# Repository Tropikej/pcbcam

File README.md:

# pcbcam

KiCad project + versioned YAML recipe → checked, machine-ready G-code for PCB
isolation milling on a **Makera Z1**, using [pcb2gcode](https://github.com/pcb2gcode/pcb2gcode)
as the CAM engine.

> **Status: v0.1, verified on a Makera Z1 (2026-11-09).** A full double-sided
> board — front + back isolation, drilling, registration bores and the tabbed
> outline — cuts and registers through the flip (both faces and the via holes
> line up). Feeds and speeds are still per-tool starting points, tuned by hand:
> air-cut first, then cut scrap.

## What it does

```
KiCad project ──► kicad-cli export (F.Cu, Edge.Cuts, Excellon mm)
                    │
recipe.yaml ──┐     ▼
tools.yaml ───┴─► preflight ── project DRC (your rules, errors only)
                    │       ── machine DRC (rules derived from your tools)
                    │       ── every hole size has a drill / milling tool
                    ▼
                 millproject ──► pcb2gcode (pinned Docker image, warnings fatal)
                    ▼
                 Z1 post-processor ──► validator ──► gcode/*.cnc + manifest.json
```

* **V-bits are modelled properly.** pcb2gcode only knows cylindrical cutters, so
  the V-bit's effective width at the cut depth (`tip + 2·depth·tan(angle/2)`, or
  your measured calibration points) is computed and passed as the diameter.
* **"Can my tools cut this board?" is a DRC.** pcbcam writes KiCad custom rules
  (minimum gap = V-bit width + margin, track width, annular ring, hole-to-hole,
  edge gap) and runs `kicad-cli pcb drc` on a scratch copy, so violations come
  back with positions, exactly like a normal DRC. Your project is never modified.
* **pcb2gcode warnings fail the build.** A "contentions" warning means the last
  cutter would eat into copper.
* **Z1 post-processing**, from pcb2gcode 3.0.4's source and the Z1 firmware docs:
  `G04 P` milliseconds → seconds, `T1`/`M6`/`M0` → `T1M6`, per-tool `S<rpm> M3`,
  drops `M0 M9 G64 G91.1 G80`; optional `G32` height-map probing before isolation.
* **Validator** rejects anything outside the profile's allowed words, inch or
  relative mode, feeds/rpm over limits, XY outside the stock, Z deeper than the
  stock, and cutting below Z0 with the spindle off.

* **Calibration boards.** Copper inside KiCad rule areas named
  `pcbcam_calibration` is exempt from the machine DRC (anything under 0.09 mm
  is still an error), and `isolation.allow_contentions: true` lets pcb2gcode cut
  into copper where the V-bit can't fit. See
  [`examples/cnc-pcb-calibration-project`](examples/cnc-pcb-calibration-project),
  generated by [`tools/gen_calibration_board.py`](tools/gen_calibration_board.py).

## Outputs

```
manufacturing-output/
├── gcode/
│   ├── 01_isolation_front.cnc
│   ├── 02_drill.cnc
│   ├── 03_milldrill.cnc        holes larger than any drill
│   ├── 04_outline.cnc          with tabs; always run last
│   ├── 05_engrave_front.cnc    label text, front (if an engrave layer is set)
│   └── 06_engrave_back.cnc     label text, back (after the flip)
├── preview/*.svg              pcb2gcode toolpath renders
├── manifest.json              versions, hashes, tools, hole assignments, run-time estimate
└── work/                      exported Gerbers, millproject, logs, DRC reports
```

`pcbcam build` also prints an **estimated run time** per job and a total, and
records it in `manifest.json` (`jobs[].est_time` and the `estimate` block). It is
machine-motion time only — feed moves at their feed rate, rapids at the profile's
`rapid_mm_min` (1200 mm/min on the Z1), plunges, and `G4` dwells (spindle
spin-up included) — plus the automatic tool-length probe per tool change. The
**manual bit swap is not counted** (it is operator-dependent); the tool-change
count is reported so you can add your own allowance. Under GitHub Actions the
estimate is also appended to the job summary (`$GITHUB_STEP_SUMMARY`).

Work zero is the **lower-left corner of the stock, on top of the copper**; the
board outline's lower-left corner sits exactly at `placement.margin_*` from it
(read from the Edge.Cuts Gerber, independent of the cutter size).

## Fixture footprints: see the stock and the pins in KiCad

A fixture file ([`fixtures/makera_z1_pins.yaml`](fixtures/makera_z1_pins.yaml))
describes the blank sizes the fixture takes and where its registration pins
are. pcbcam turns it into KiCad footprints:

```sh
uv run pcbcam fixture-footprint fixtures/makera_z1_pins.yaml --out kicad/pcbcam-fixtures.pretty
```

Each footprint (`Stock_100x160_Pins4mm`, ...) is graphics only, on the
fixture's user layer (`User.10`): the stock outline, the area the board may use,
the pins with their keep-out circles, the flip axis and work zero. No pads, no
holes, so nothing reaches the Gerbers or the drill file, and KiCad's DRC has
nothing to report on it.

The KiCad 10 KiBot template does all of step 1 below with
`./run_kibot.sh --stackup makera_z1_2l`, places the footprint and installs
starter `manufacturing/` files. It ships its own copy of the library
(`kibot_resources/footprints/pcbcam-fixtures.pretty`): copy the regenerated
footprints there when the fixture changes.

To use it:

1. KiCad: add `kicad/pcbcam-fixtures.pretty` to the footprint libraries
   (nickname `pcbcam-fixtures`), and add layer `User.10` named `Fixture`
   (Board Setup > Board Editor Layers). Best done once, in your template.
2. Place the footprint, lock it, and draw Edge.Cuts inside the dashed area.
3. Recipe: `fixture: fixture.yaml` (a copy of the fixture file) and the same
   stock size as the footprint.

Then **the footprint's origin is work zero**: the board is cut where it is
drawn, and `placement.margin_*` is ignored. The build fails if the footprint is
missing, rotated, flipped or older than the fixture file, if the stock size
differs from the recipe, or if the outline comes too close to the stock edge or
to a pin (pin radius + `pin_clearance_mm`, checked on the outline's bounding
box).

## Engraved labels

Add text (connector names, a logo) and have a V-bit engrave it, in the same
build. Draw the labels in KiCad's **default stroke font** on a dedicated layer,
then point the recipe at it:

```yaml
engrave:
  tool: vbit_20_0.2     # any V-bit or end mill in tools.yaml
  depth_mm: 0.10        # shallow; must be less than the stock thickness
  front_layer: User.11  # cut as drawn
  back_layer: User.12   # mirrored about the fixture flip axis; omit to skip
```

pcbcam exports the layer to DXF (stroke glyphs plot as their pen path, not
filled outlines), chains the strokes to minimise pen lifts, and traces them at
`depth_mm`, registered to the copper by the same work offset as every other job.
`back_layer` is mirrored left-right (about the flip axis) like the back
isolation will be, so **tick the text's "Mirrored" box** in KiCad for back
labels: KiCad doesn't auto-mirror a plain user layer the way it does B.SilkS,
and that one tick cancels pcbcam's mirror so the letters read correctly when you
look straight at the finished back face (the text looks backwards in the editor —
that's right). Run `06_engrave_back.cnc` after the flip (it needs a fixture, for
the axis). Keep text **≥ ~2 mm tall** and short — a 0.2 mm V-bit can't resolve
fine print.

## Usage

```sh
uv sync
docker build -t pcbcam/pcb2gcode:3.0.4 docker/pcb2gcode

# in a KiCad project containing manufacturing/recipe.yaml + tools.yaml
uv run pcbcam tools  path/to/project   # resolved tools + the clearance they need
uv run pcbcam check  path/to/project   # export + DRC + hole checks only
uv run pcbcam build  path/to/project   # everything
```

Start from [`examples/manufacturing/`](examples/manufacturing). Recipes are strict:
unknown keys are errors and every value has its unit in its name.

Environment:

| Variable | Default | Purpose |
|---|---|---|
| `KICAD_CLI` | PATH, then `C:\Program Files\KiCad\*\bin` | kicad-cli to use |
| `PCBCAM_PCB2GCODE_IMAGE` | `pcbcam/pcb2gcode:3.0.4` | Docker image |
| `PCBCAM_PCB2GCODE_BIN` | unset | run a local pcb2gcode instead of Docker |

## Not done yet

* Slots / oval holes (reported as errors).
* `G32` height-map probing is experimental and still unverified: which tool the
  Z1 probes with, and whether Makera Studio keeps the compensation for an
  imported file. The verified flow uses Studio's own 5x5 auto-leveling instead.

## Tests

```sh
uv run pytest            # unit tests
uv run pytest -m integration   # needs kicad-cli + the Docker image
```

## License & credits

pcbcam is released under the [MIT License](LICENSE).

The CAM engine is [**pcb2gcode**](https://github.com/pcb2gcode/pcb2gcode) — a
separate program, **licensed GPLv3**, that pcbcam invokes at arm's length (a
subprocess / the pinned Docker image). pcbcam contains none of its code, so
pcbcam's own MIT license is unaffected. `docker/pcb2gcode/Dockerfile` builds
pcb2gcode from a pinned upstream tag; if you distribute that built image it
carries pcb2gcode's GPLv3 (make the corresponding source available). Many thanks
to the pcb2gcode authors — pcbcam would not exist without it.

Export and design-rule checks use [KiCad](https://www.kicad.org/)'s `kicad-cli`.

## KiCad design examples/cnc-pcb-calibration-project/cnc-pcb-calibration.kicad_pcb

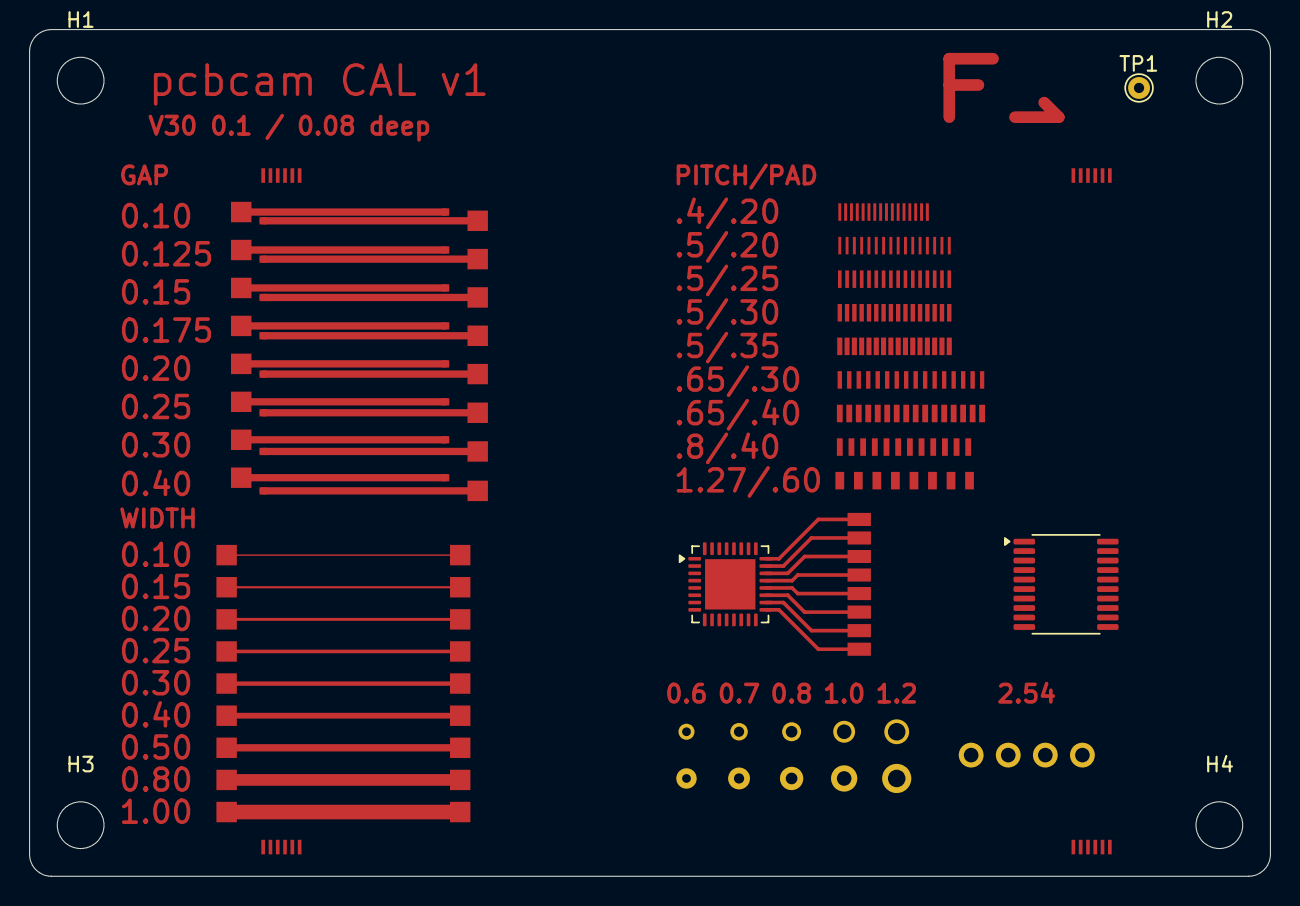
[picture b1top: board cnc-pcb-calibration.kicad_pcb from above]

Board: 2 copper layers, 85.0 x 58.0 mm, 40 parts (0 on the bottom side), 33 nets.

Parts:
CAL1: gap 0.1
CAL2: gap 0.125
CAL3: gap 0.15
CAL4: gap 0.175
CAL5: gap 0.2
CAL6: gap 0.25
CAL7: gap 0.3
CAL8: gap 0.4
CAL9: track 0.1
CAL10: track 0.15
CAL11: track 0.2
CAL12: track 0.25
CAL13: track 0.3
CAL14: track 0.4
CAL15: track 0.5
CAL16: track 0.8
CAL17: track 1.0
CAL18: pitch 0.4 pad 0.2
CAL19: pitch 0.5 pad 0.2
CAL20: pitch 0.5 pad 0.25
CAL21: pitch 0.5 pad 0.3
CAL22: pitch 0.5 pad 0.35
CAL23: pitch 0.65 pad 0.3
CAL24: pitch 0.65 pad 0.4
CAL25: pitch 0.8 pad 0.4
CAL26: pitch 1.27 pad 0.6
CAL27: QFN fanout test pads
CAL28: hole sizes
CAL29: 2.54 header
CAL30: witness TL
CAL31: witness TR
CAL32: witness BL
CAL33: witness BR
CAL_U1: QFN-32-1EP_5x5mm_P0.5mm_EP3.45x3.45mm
CAL_U2: TSSOP-20_4.4x6.5mm_P0.65mm
H1, H2, H3, H4: M3; MountingHole_3.2mm_M3
TP1: GND; TestPoint_THTPad_D1.5mm_Drill0.7mm

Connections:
CAL_CAL_U1_17: CAL27.8, CAL_U1.17
CAL_CAL_U1_18: CAL27.7, CAL_U1.18
CAL_CAL_U1_19: CAL27.6, CAL_U1.19
CAL_CAL_U1_20: CAL27.5, CAL_U1.20
CAL_CAL_U1_21: CAL27.4, CAL_U1.21
CAL_CAL_U1_22: CAL27.3, CAL_U1.22
CAL_CAL_U1_23: CAL27.2, CAL_U1.23
CAL_CAL_U1_24: CAL27.1, CAL_U1.24
CAL_GAP0_A: CAL1.1, CAL1.3
CAL_GAP0_B: CAL1.2, CAL1.4
CAL_GAP1_A: CAL2.1, CAL2.3
CAL_GAP1_B: CAL2.2, CAL2.4
CAL_GAP2_A: CAL3.1, CAL3.3
CAL_GAP2_B: CAL3.2, CAL3.4
CAL_GAP3_A: CAL4.1, CAL4.3
CAL_GAP3_B: CAL4.2, CAL4.4
CAL_GAP4_A: CAL5.1, CAL5.3
CAL_GAP4_B: CAL5.2, CAL5.4
CAL_GAP5_A: CAL6.1, CAL6.3
CAL_GAP5_B: CAL6.2, CAL6.4
CAL_GAP6_A: CAL7.1, CAL7.3
CAL_GAP6_B: CAL7.2, CAL7.4
CAL_GAP7_A: CAL8.1, CAL8.3
CAL_GAP7_B: CAL8.2, CAL8.4
CAL_W0: CAL9.1, CAL9.2
CAL_W1: CAL10.1, CAL10.2
CAL_W2: CAL11.1, CAL11.2
CAL_W3: CAL12.1, CAL12.2
CAL_W4: CAL13.1, CAL13.2
CAL_W5: CAL14.1, CAL14.2
CAL_W6: CAL15.1, CAL15.2
CAL_W7: CAL16.1, CAL16.2
CAL_W8: CAL17.1, CAL17.2
